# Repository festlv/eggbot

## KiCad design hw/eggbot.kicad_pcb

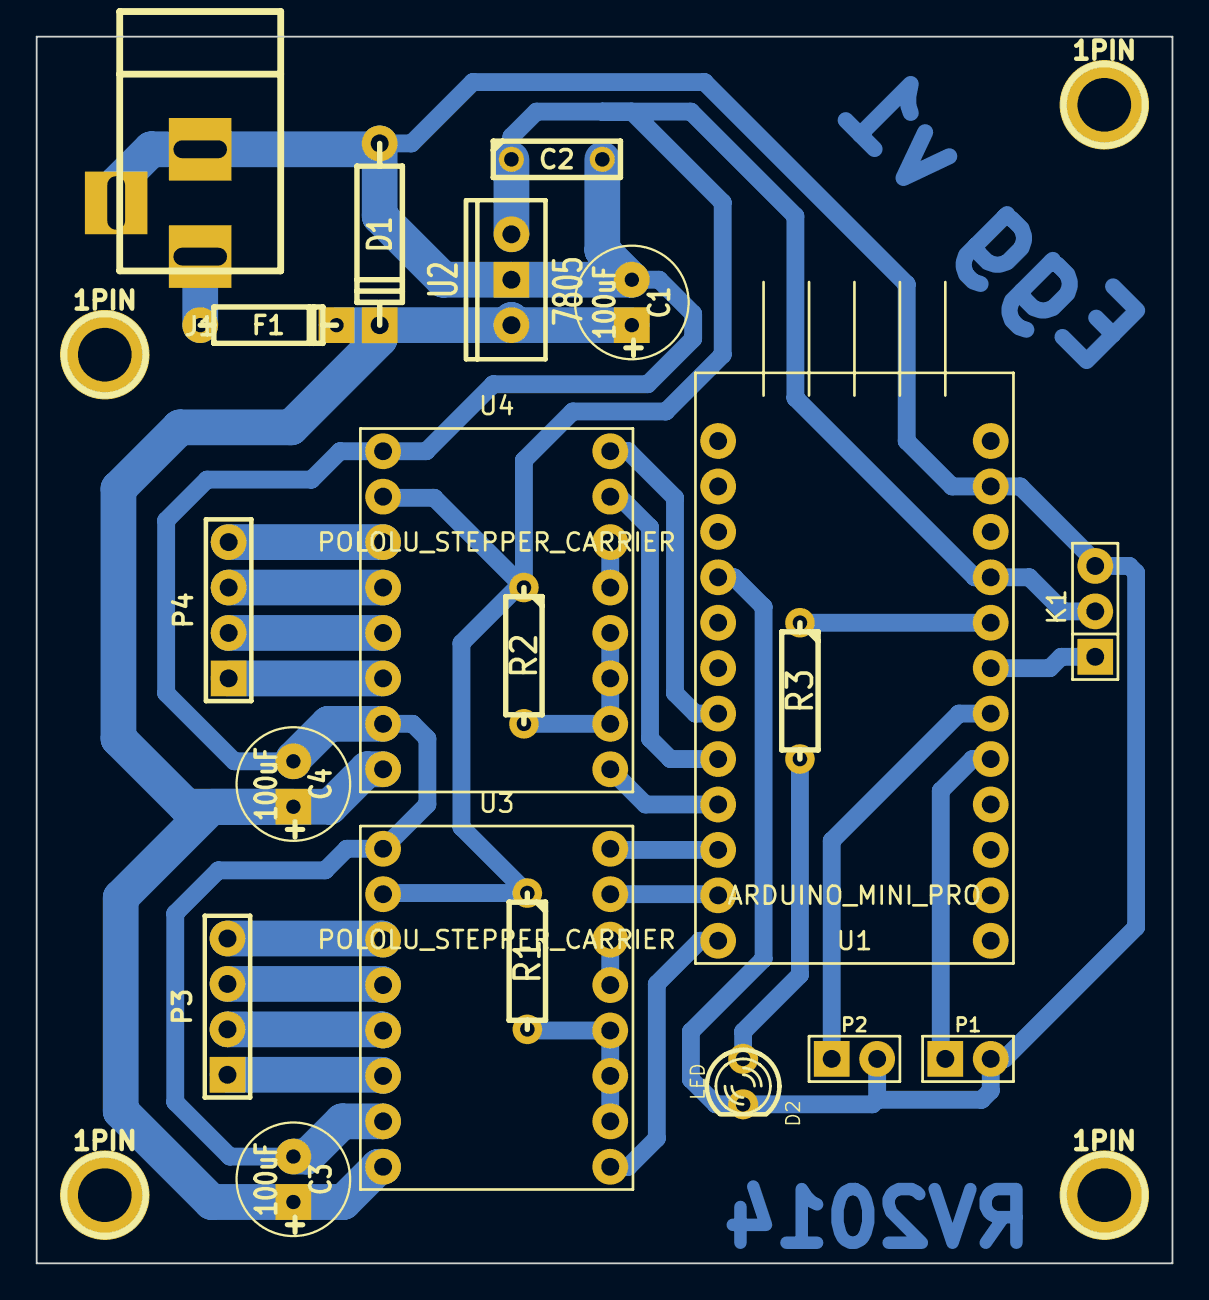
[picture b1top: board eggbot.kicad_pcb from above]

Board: 2 copper layers, 63.5 x 68.6 mm, 24 parts (0 on the bottom side), 27 nets.

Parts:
1PIN, 1PIN#2, 1PIN#3, 1PIN#4: P***; 1pin
C1, C3, C4: 100uF; C1V7
C2: 10uF; C2
D1: DIODE; D4
D2: LED; LED-3MM
F1: 2A; D3
J1: JACK_2P; BARREL_JACK
K1: CONN_3; PIN_ARRAY_3X1
P1, P2: CONN_2; PIN_ARRAY_2X1
P3, P4: CONN_4; PIN_ARRAY_4x1
R1, R2: 10K; R3-LARGE_PADS
R3: 470R; R3-LARGE_PADS
U1: ARDUINO_MINI_PRO; ARDUINO_MINI
U2: 7805; LM78XXV
U3, U4: POLOLU_STEPPER_CARRIER; DRV8825_CARRIER

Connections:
+5V: C2.1, K1.2, R1.1, R2.1, U1.25, U2.VO, U3.10, U4.10
+12V: C1.1, C3.1, C4.1, D1.2, F1.2, U2.VI, U3.16, U4.16
/DIR_1: U1.10, U3.8
/DIR_2: U1.7, U4.8
/END_SW_1: P1.1, U1.21
/END_SW_2: P2.1, U1.22
/EN_1: U1.12, U3.1
/EN_2: U1.9, U4.1
/SERVO: K1.1, U1.23
/STEP_1: U1.11, U3.7
/STEP_2: U1.8, U4.7
GND: C1.2, C2.2, C3.2, C4.2, D1.1, D2.2, J1.1, J1.2, K1.3, P1.2, P2.2, U1.4, U1.27, U2.GND, U3.9, U3.15, U4.9, U4.15
unnamed: R1.2, U3.2, U3.3, U3.4
unnamed: U4.5, U4.6
unnamed: U3.5, U3.6
unnamed: R2.2, U4.2, U4.3, U4.4
unnamed: R3.1, U1.24
unnamed: D2.1, R3.2
unnamed: P4.1, U4.14
unnamed: P4.2, U4.13
unnamed: P4.3, U4.12
unnamed: P4.4, U4.11
unnamed: F1.1, J1.3
unnamed: P3.3, U3.12
unnamed: P3.4, U3.11
unnamed: P3.2, U3.13
unnamed: P3.1, U3.14

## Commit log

2014-04-03 Committing G-code for milling PCB
2014-04-08 Latest revision of schematics
2014-04-14 First revision of firmware
2014-10-28 Added schematics
2014-10-28 Made servo movements smoother
